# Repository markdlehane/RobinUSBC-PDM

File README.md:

# USB-C data and power supply.

## An adaptor that allows connection from a usb power supply or laptop.

It's available as a kit or a premade module on [Tindie](https://www.tindie.com/products/36667/).

This adaptor provides 5v & 3.3v @1A from a USB-C connector. It also provides USB D+ and D- pins so that it can be used with a laptop or computer to provide power and data. I developed this board with the assistance of the wonderful people at [PCBWay](https://www.pcbway.com/) who enabled me to take my early design and turn it into a module that I use in every project I make now.  It's a huge time saver and makes the process of connecting my development boards to a laptop, very simple.

## Why did you make it?

I designed this module because I was tired of the standard breadboard power supplies that simply provide 5v or 3.3v from a barrel jack. The old style supplies were limited because, even if I use USB as a supply, I didn't have a data connection. 

## What makes it special?

This module is easy to use on a breadboard, can be integrated directly into a PCB project with a jumper and provides a data pathway to your embedded device. There is a transient voltage suppression device on the board to give added project from voltage spikes as the cable is connected.

## Module design

I designed this board because I have been developing project with ESP32S3 modules. These made a USB data connection immediately available, like many other alternatives, and I wanted to simplify my prototyping and development process through simplification. 

The module is supplied with an [AZ1117I](https://www.diodes.com/assets/Datasheets/AZ1117I.pdf) 3.3v LDO and the 5v is provided directly by the USB-C connection (which uses 2 5k1 1% resistors to negotiate the voltage). There is an LED on the board to indicate that 5v power is connected by this can be disconnected through a solder bridge so that it can be disabled when power must be stricly controlled.

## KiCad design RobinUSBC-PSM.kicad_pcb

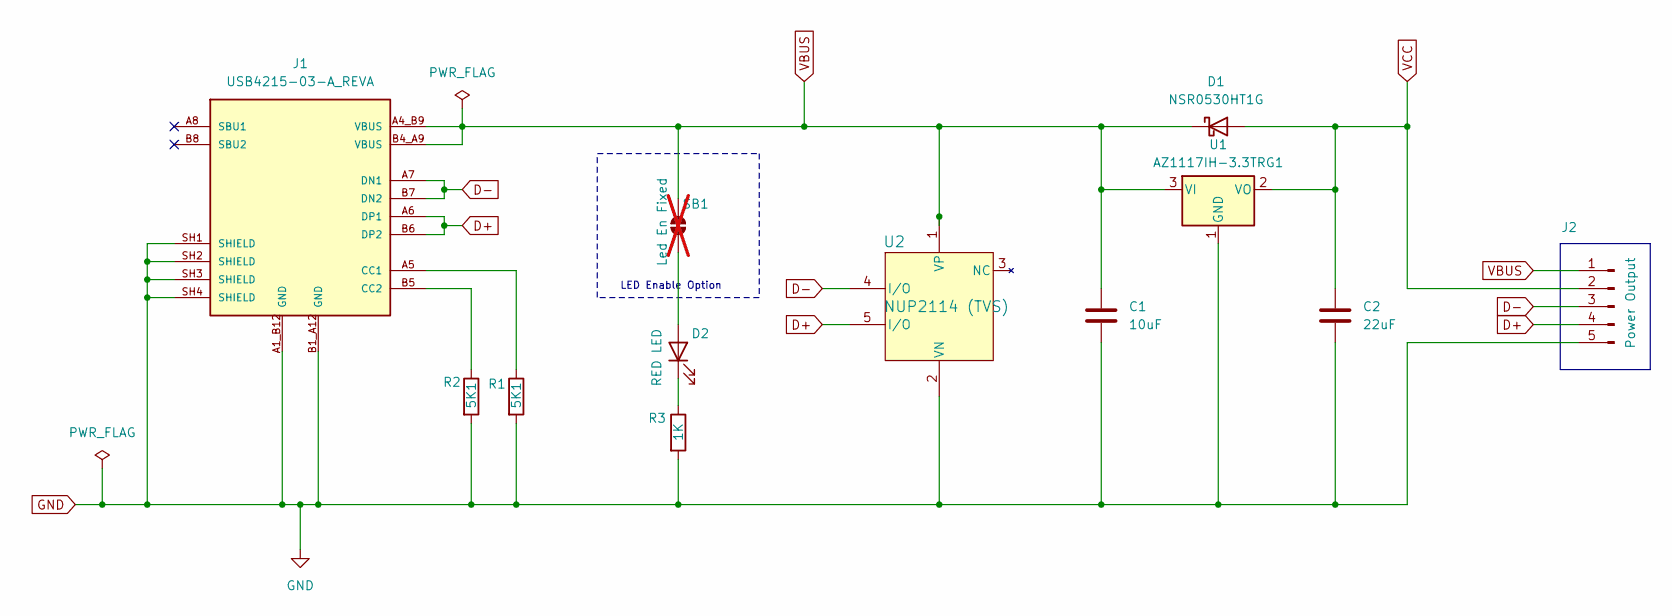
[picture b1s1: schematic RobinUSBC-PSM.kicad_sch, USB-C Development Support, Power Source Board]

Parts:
C1: 10uF; C_0805_2012Metric; PartNo CL21B106KOQNNNE
C2: 22uF; C_0805_2012Metric; PartNo GRM21BZ71A226ME15L
D1: NSR0530HT1G; D_SOD-323_HandSoldering; PartNo NSR0530HT1G
D2: RED LED; D_1206_3216Metric_Pad1.42x1.75mm_HandSolder; PartNo 150120RS75000
J1: USB4215-03-A_REVA; GCT_USB4215-03-A_REVA; PARTREV A; DigiKey_Part_Number 2073-USB4215-03-ATR-ND
J2: Power Output; PinHeader_1x05_P2.54mm_Vertical; PartNo PH1-10-UA
R1, R2: 5K1; R_0603_1608Metric; PartNo RC0603FR-075K1L
R3: 1K; R_0603_1608Metric; PartNo RC0603JR-071KL
SB1: Led En Fixed; SolderJumper-2_P1.3mm_Open_RoundedPad1.0x1.5mm; PartNo Solder Jumper, 2-pole, open; not fitted
U1: AZ1117IH-3.3TRG1; SOT-223-3_TabPin2; PartNo AZ1117IH-3.3TRG1
U2: NUP2114 (TVS); SOT-553_1P65X1P25_ONS; PartNo NUP2114UPXV5T1G

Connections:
D+: J1.A6 (DP1), J1.B6 (DP2), J2.4, U2.5 (I/O)
D-: J1.A7 (DN1), J1.B7 (DN2), J2.3, U2.4 (I/O)
GND: C1.2, C2.2, J1.A1_B12 (GND), J1.B1_A12 (GND), J1.SH1 (SHIELD), J1.SH2 (SHIELD), J1.SH3 (SHIELD), J1.SH4 (SHIELD), J2.5, R1.2, R2.2, R3.2, U1.1 (GND), U2.2 (VN)
unnamed: D2.2 (A), SB1.1 (A)
unnamed: D2.1 (K), R3.1
unnamed: J1.A5 (CC1), R1.1
unnamed: J1.B5 (CC2), R2.1
VBUS: C1.1, D1.1 (K), J1.A4_B9 (VBUS), J1.B4_A9 (VBUS), J2.1, SB1.2 (B), U1.3 (VI), U2.1 (VP)
VCC: C2.1, D1.2 (A), J2.2, U1.2 (VO)

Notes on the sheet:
LED Enable Option

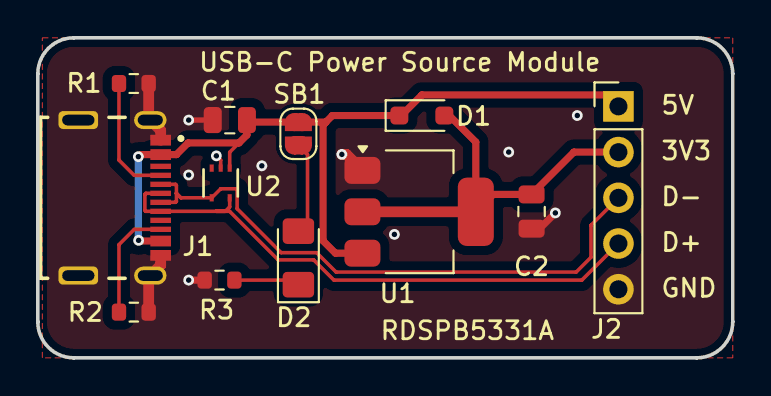
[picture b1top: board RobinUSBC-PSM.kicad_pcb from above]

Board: 2 copper layers, 38.6 x 17.8 mm, 12 parts (0 on the bottom side), 9 nets.

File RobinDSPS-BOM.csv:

Reference,Value,Description,PartNo,MANUFACTURER
C1,10uF,10 µF ±10% 16V Ceramic Capacitor X7R 0805 (2012 Metric),CL21B106KOQNNNE,Samsung Electro-Mechanics
U1,AZ1117IH-3.3TRG1,"1A 20V Fixed LDO Linear Regulator, 3.3V, SOT-89/SOT-223/TO-220/TO-252/TO-263",AZ1117IH-3.3TRG1,Diodes Incorporated
R3,1K,1k 0604 Resistor,RC0603JR-071KL,YAGEO
R1,5K1,5K1 0603 Resistor,RC0603FR-075K1L,YAGEO
R2,5K1,5K1 0603 Resistor,RC0603FR-075K1L,YAGEO
C2,22uF,CAP CER 22UF 10V X7R 0805,GRM21BZ71A226ME15L,Murata Electronics
J1,USB4215-03-A_REVA,CONN RCP USB2.0 TYP C 24P SMD RA,USB4105-GF-A-060,Global Connector Technology
J2,Power Output,"Connector Header Through Hole 10 position 0.100"" (2.54mm)",PH1-10-UA,Adam Tech
D2,RED LED,LED RED CLEAR 1206 SMD,150120RS75000,WÃ¼rth Elektronik
D1,NSR0530HT1G,"Schottky diode, 30V, 500mA",NSR0530HT1G,onsemi
U2,NUP2114 (TVS),TVS Protection Diode,NUP2114UPXV5T1G,Diodes Incorporated

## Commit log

2024-11-24 Update .gitignore rules
    Added local ignored directory
2024-11-24 Added media files.
    Added 4 images.
2024-11-24 Create README.md
    Created readme with project description
2024-11-24 Update README.md
    Additional images.
2024-11-24 Update README.md
    Added Tindie link
2024-11-27 Project setup
2024-11-27 Update README.md
    Added images

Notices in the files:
RobinUSBC-PSM.kicad_pcb:
Copyright (c) 2024, Robin Electronics Ltd.  All rights reserved.
